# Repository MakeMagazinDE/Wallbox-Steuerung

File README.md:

Maker Media GmbH

***

# Photovoltaik an der E-Auto-Wallbox

### Überschuss-Laden mit der eigenen Wallbox

Die KfW-Förderung für Wallboxen macht hauseigene Ladeterminals attraktiv wie nie. Wer zudem schon eine Photovoltaik-Anlage installiert hat, kann sein Auto kostenfrei mit Solarstrom laden. Voraussetzung ist allerdings eine intelligente Steuerung – wenn die fehlt, rüstet man einfach unsere ESP8266-Ladeautomatik nach. 

### Dateien:

* eagle pcb (Verzeichnis) - Eagle-Dateien für Platinenversion
* pv_charger_mit_SD_23092021-goe-SW-ab051.4 (Verzeichnis) - Projektdateien für ESP8266 auf Arduino-IDE
* Schaltplan Wemos D1 mini.jpg - Schaltplane, hohe Auflösung wie im Heft abgedruckt

Den vollständigen Artikel mit der Bauanleitung gibt es in der [Make-Ausgabe 5/21 ab Seite 104](https://www.heise.de/select/make/2021/5).

# Photovoltaik an der E-Auto-Wallbox - reloaded

### Überschuss-Laden mit der eigenen Wallbox, Teil 2

Teil 2 in [Make-Ausgabe 2/22 ab Seite 52](https://www.heise.de/select/make/2022/6) ergänzt das Projekt um einen zweiten Lösungsansatz, der ohne zusätzlichen Energiezähler auskommt und stattdessen den aktuellen Verbrauch aus dem "Smart Meter" des Stromanbieters ausliest. Software und Layout finden Sie im Unterordner "Wallbox Teil 2".

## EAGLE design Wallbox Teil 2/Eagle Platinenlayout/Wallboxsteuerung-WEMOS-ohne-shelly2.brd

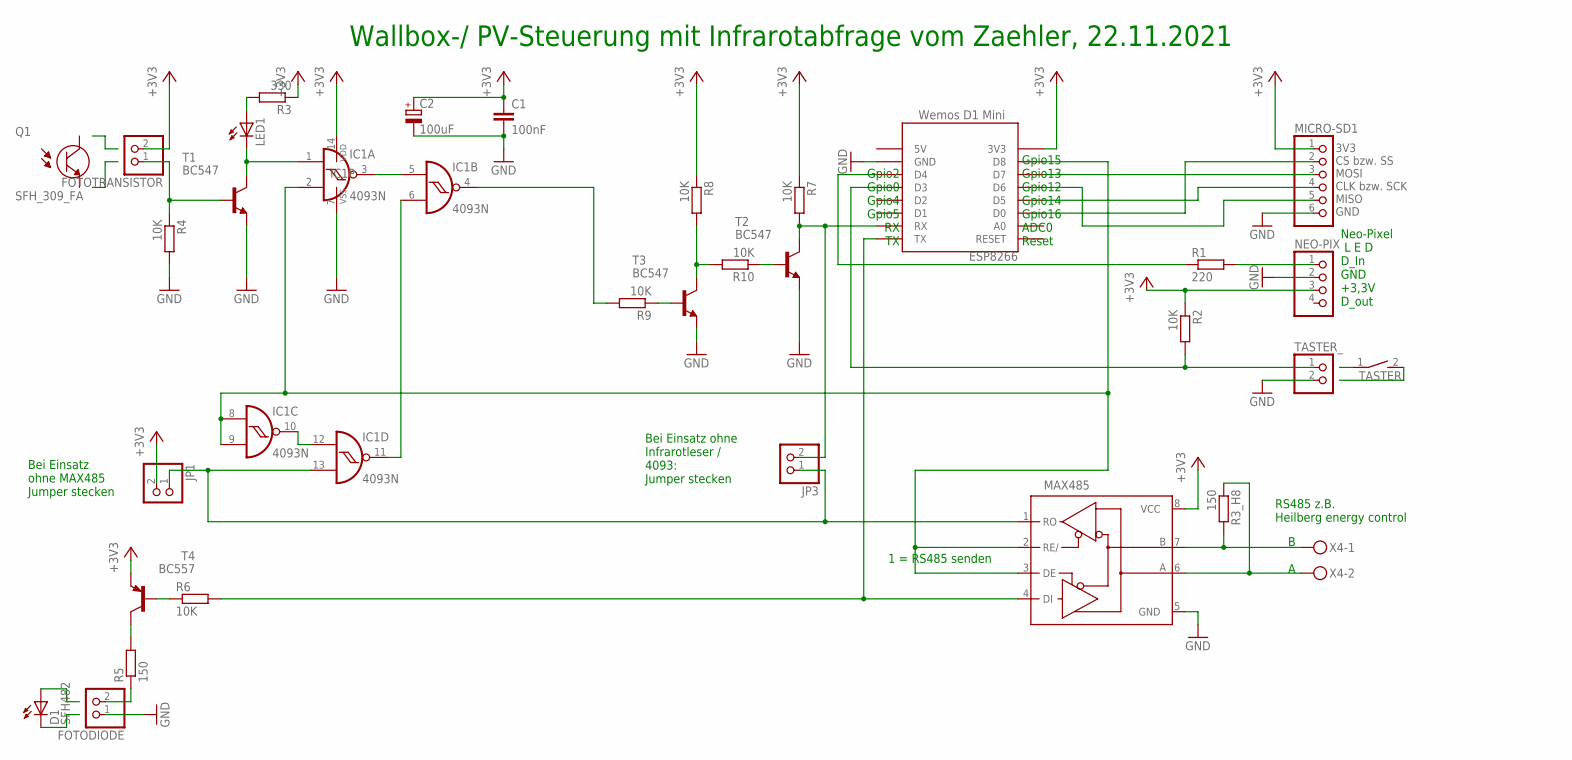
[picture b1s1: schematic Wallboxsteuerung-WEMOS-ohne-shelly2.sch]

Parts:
C1: 100nF; C050-045X075
C2: 100uF; E5-6
D1: SFH482
ESP8266: Wemos D1 Mini; WEMOS-D1-MINI
FOTODIODE: PINHD-1X2; 1X02
FOTOTRANSISTOR: PINHD-1X2; 1X02
IC1: 4093N; DIL14
JP1, JP3: PINHD-1X2; 1X02
LED1: LED5MM
MAX485: MAX3468CPA; DIL08
MICRO-SD1: PINHD-1X6; 1X06
NEO-PIX: PINHD-1X4; 1X04
Q1: SFH_309_FA; XDCR_SFH_309_FA
R1: 220; 0309V
R2, R4, R6, R7, R8, R9, R10: 10K; 0309V
R3: 330; 0309V
R3_H8, R5: 150; 0309V
T1, T2, T3: BC547; TO92
T4: BC557; TO92
TASTER: DS01E; DS-01
TASTER_: PINHD-1X2; 1X02
X4: MKDSN1,5/2-5,08

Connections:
+3V3: C1.1, C2.+, ESP8266.3V3, FOTOTRANSISTOR.2, IC1.14 (VDD), JP1.2, MAX485.8 (VCC), MICRO-SD1.1, NEO-PIX.3, R2.1, R3.1, R7.1, R8.1, T4.1 (E)
GND: C1.2, C2.-, ESP8266.GND, FOTODIODE.1, IC1.7 (VSS), MAX485.5 (GND), MICRO-SD1.6, NEO-PIX.2, R4.2, T1.1 (E), T2.1 (E), T3.1 (E), TASTER_.2
unnamed: ESP8266.D4, R1.1
unnamed: FOTOTRANSISTOR.1, R4.1, T1.2 (B)
unnamed: IC1.1 (I0), LED1.K (C), T1.3 (C)
unnamed: IC1.3 (O), IC1.5 (I0)
unnamed: ESP8266.D8, IC1.2 (I1), IC1.8 (I0), IC1.9 (I1), MAX485.2 (RE/), MAX485.3 (DE)
unnamed: R5.2, T4.3 (C)
unnamed: IC1.4 (O), R9.2
unnamed: ESP8266.TX, MAX485.4 (DI), R6.2
unnamed: IC1.6 (I1), IC1.11 (O)
unnamed: FOTODIODE.2, R5.1
unnamed: R6.1, T4.2 (B)
unnamed: IC1.10 (O), IC1.12 (I0)
unnamed: ESP8266.RX, JP3.2, R7.2, T2.3 (C)
unnamed: R8.2, R10.2, T3.3 (C)
unnamed: R10.1, T2.2 (B)
unnamed: R9.1, T3.2 (B)
unnamed: LED1.A, R3.2
unnamed: IC1.13 (I1), JP1.1, JP3.1, MAX485.1 (RO)
unnamed: NEO-PIX.1, R1.2
unnamed: ESP8266.D3, R2.2, TASTER_.1
unnamed: ESP8266.D0, MICRO-SD1.2
unnamed: ESP8266.D7, MICRO-SD1.3
unnamed: ESP8266.D5, MICRO-SD1.4
unnamed: ESP8266.D6, MICRO-SD1.5
unnamed: MAX485.7 (B), R3_H8.2, X4.1
unnamed: MAX485.6 (A), R3_H8.1, X4.2

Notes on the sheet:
Wallbox-/ PV-Steuerung mit Infrarotabfrage vom Zaehler, 22.11.2021
3V3 CS bzw. SS MOSI CLK bzw. SCK MISO GND
Neo-Pixel L E D D_In GND +3,3V D_out
B A
RS485 z.B. Heilberg energy control
Bei Einsatz ohne MAX485 Jumper stecken
Bei Einsatz ohne Infrarotleser / 4093: Jumper stecken
Gpio15 Gpio13 Gpio12 Gpio14 Gpio16 ADC0 Reset
Gpio2 Gpio0 Gpio4 Gpio5 RX TX
1 = RS485 senden

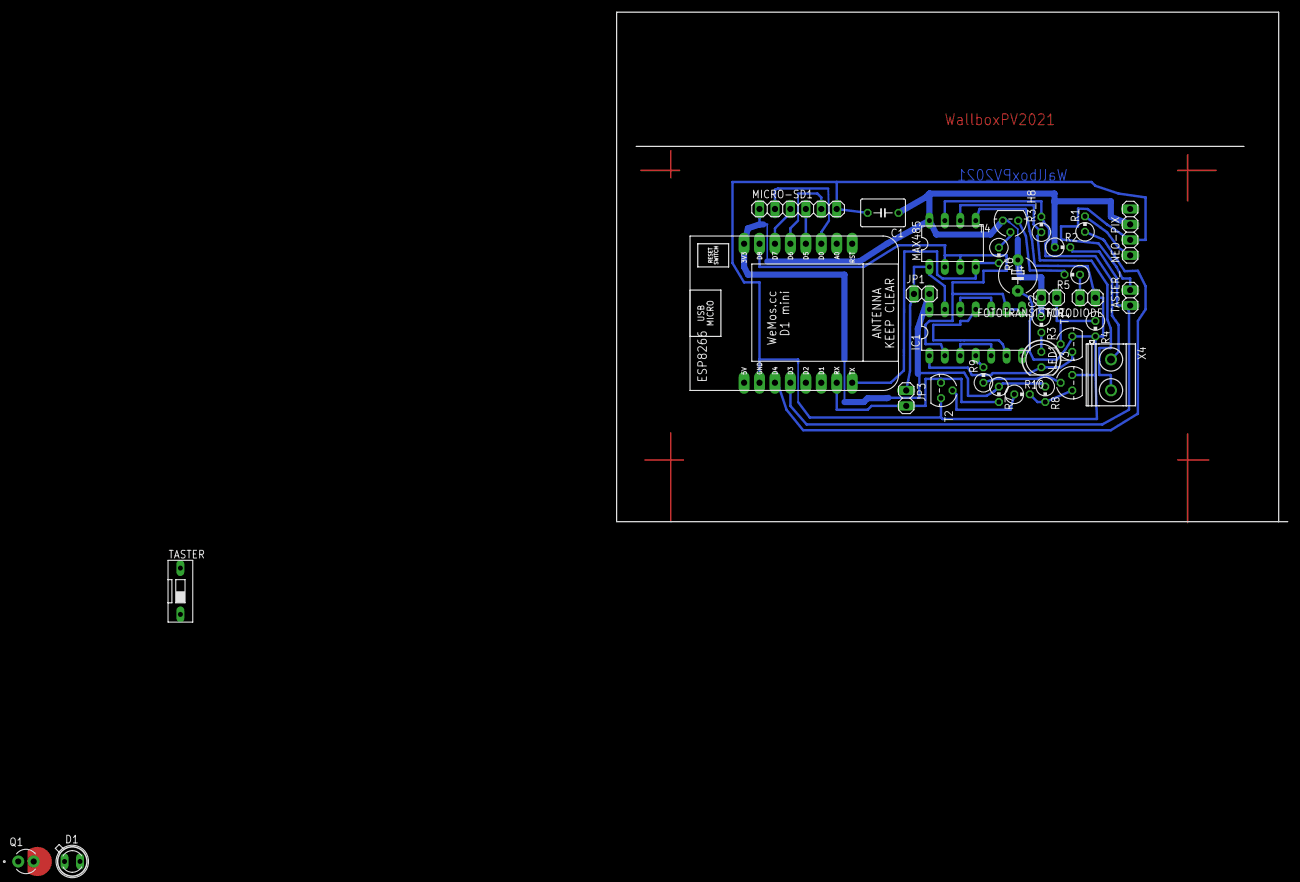
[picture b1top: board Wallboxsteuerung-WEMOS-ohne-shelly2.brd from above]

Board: 2 copper layers, 110.4 x 83.8 mm, 32 parts (0 on the bottom side), 28 nets.

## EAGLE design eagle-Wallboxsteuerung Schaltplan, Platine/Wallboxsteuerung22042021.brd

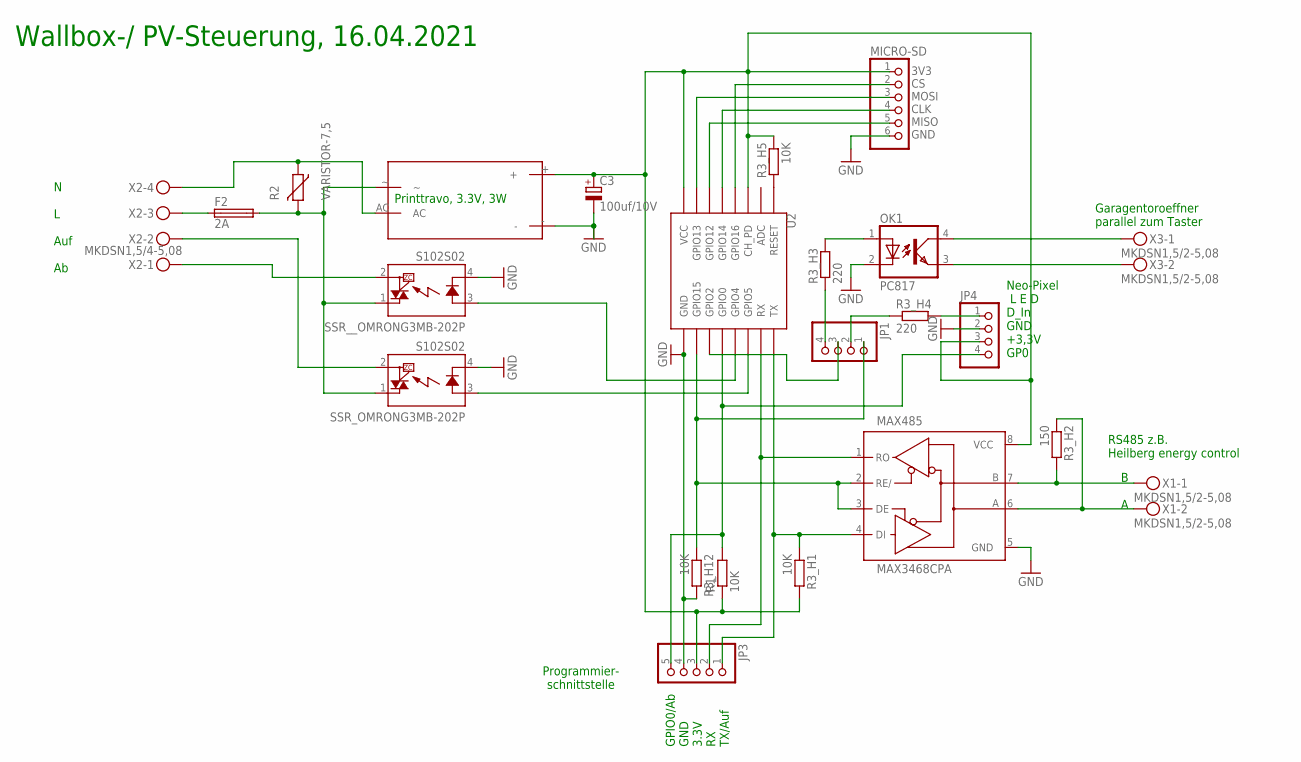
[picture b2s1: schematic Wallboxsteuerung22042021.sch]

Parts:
C3: 100uf/10V; E2,5-7
F2: 2A; LITTLEFUSE
JP1, JP4: PINHD-1X4; 1X04
JP3: PINHD-1X5; 1X05
MAX485: MAX3468CPA; DIL08
MICRO-SD: PINHD-1X6; 1X06
OK1: PC817; DIL04
PRINTTRAFO3.3V,_3W: PRINTTRAFO
R1: 10K; 0207/7
R2: VARISTOR-7,5; R-7,5
R3_H1, R3_H5: 10K; 0309V
R3_H2: 150; 0309V
R3_H3, R3_H4: 220; 0309V
R3_H12: 10K; 0207/2V
SSR_OMRONG3MB-202P: S102S02; S202S02
SSR__OMRONG3MB-202P: S102S02; S202S02
U2: ESP12SMD; ESP12-SMD
X1, X3: MKDSN1,5/2-5,08
X2: MKDSN1,5/4-5,08

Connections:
GND: C3.-, JP3.4, JP4.2, MAX485.5 (GND), MICRO-SD.6, OK1.2 (C), PRINTTRAFO3.3V,_3W.-, R3_H12.2, SSR_OMRONG3MB-202P.4 (K), SSR__OMRONG3MB-202P.4 (K), U2.GND
unnamed: SSR_OMRONG3MB-202P.3 (A), U2.GPIO4 (GPIO5)
unnamed: F2.1, X2.3
unnamed: SSR__OMRONG3MB-202P.3 (A), U2.GPIO5 (GPIO4)
unnamed: SSR_OMRONG3MB-202P.2 (DS2), X2.2
unnamed: R3_H5.2, U2.RESET
unnamed: JP3.2, MAX485.1 (RO), U2.RXD0 (RX)
unnamed: PRINTTRAFO3.3V,_3W.AC, R2.1, X2.4
unnamed: JP4.1, R3_H4.2
unnamed: JP1.3, U2.GPIO2
unnamed: MICRO-SD.4, U2.GPIO14
unnamed: JP3.5, JP4.4, R1.2, U2.GPIO0
unnamed: F2.2, PRINTTRAFO3.3V,_3W.~, R2.2, SSR_OMRONG3MB-202P.1 (DS1), SSR__OMRONG3MB-202P.1 (DS1)
unnamed: SSR__OMRONG3MB-202P.2 (DS2), X2.1
unnamed: MICRO-SD.5, U2.GPIO12
unnamed: MICRO-SD.3, U2.GPIO13
unnamed: JP1.4, R3_H3.1
unnamed: MICRO-SD.2, U2.GPIO16
unnamed: JP3.1, MAX485.4 (DI), R3_H1.1, U2.TXD0 (TX)
unnamed: OK1.1 (A), R3_H3.2
unnamed: MAX485.7 (B), R3_H2.2, X1.1
unnamed: MAX485.6 (A), R3_H2.1, X1.2
unnamed: OK1.3 (EMIT), X3.2
unnamed: OK1.4 (COL), X3.1
unnamed: JP1.2, R3_H4.1
unnamed: JP1.1, MAX485.2 (RE/), MAX485.3 (DE), R3_H12.1, U2.GPIO15
unnamed: C3.+, JP3.3, JP4.3, MAX485.8 (VCC), MICRO-SD.1, PRINTTRAFO3.3V,_3W.+, R1.1, R3_H1.2, R3_H5.1, U2.CH_PD, U2.VCC

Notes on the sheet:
Printtravo, 3.3V, 3W
N L Auf Ab
Wallbox-/ PV-Steuerung, 16.04.2021
GPIO0/Ab GND 3.3V RX TX/Auf
Programmier- schnittstelle
3V3 CS MOSI CLK MISO GND
B A
Garagentoroeffner parallel zum Taster
RS485 z.B. Heilberg energy control
Neo-Pixel L E D D_In GND +3,3V GP0

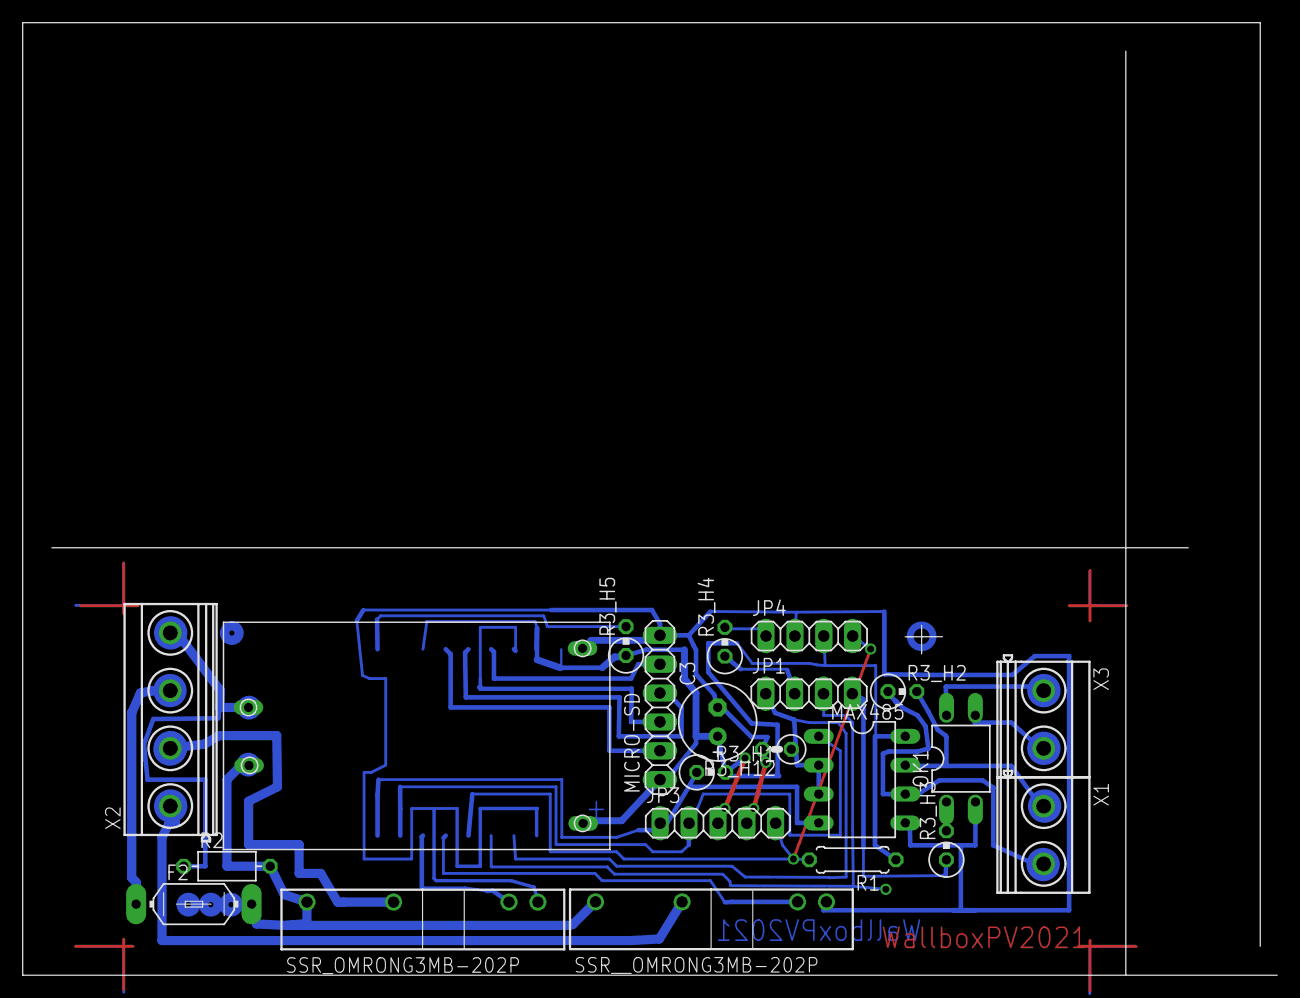
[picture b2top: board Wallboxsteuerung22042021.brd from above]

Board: 2 copper layers, 110.4 x 83.8 mm, 23 parts (1 on the bottom side), 27 nets.

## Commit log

2021-10-19 new version
    für Go-e ab der Softwareversion 051.4
2021-10-19 new version
    Go-e ab der Softwareversion 051.4
2022-04-04 Ergänzungen Teil 2
